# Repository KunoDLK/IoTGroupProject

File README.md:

# Project:

## Waste Management Optimization:

Problem: Static bin collection routes can leave many bins overflowing
Solution: Create a smart waste management system with fill-level so the council can optimes bin collection
Sensors: Ultrasonic distance sensors measure bin fill levels; Weight Sensor to approximate waste density; Air Monitoring for potential pollution cause by waste

## Work split:

Kuno:
- Hardware:
  - PCB
  - mounting + assembly
- Firmware:
  - Reading sensors
  - Sending data to cloud
- Creating Fake Data

Mark & Andrea:
- Cloud:
  - Server
- Application:
  - Collecting data from MQTT
  - displaying the data
  - Figure out which bin needs to be collected next

## The data:

- Current Data:
  - Temp
  - humidity
  - Fill Level
  - Weight
  - Density
- Daily Data:
  - Day high Temp
  - Day Low Temp
  - Day Fill delta
- Counters:
  - Time Since Emptied
  - Time Since Full
  - Number of fills
- Server Data
  - trends ect.

## MQTT:

URL:
c79e2ea5e65e40f6b79ba3a3aad7c19f.s1.eu.hivemq.cloud
Port:
8883
Websocket Port:
8884

User:admin
Password:Password1  

## MQTT Websocket Client
https://www.hivemq.com/demos/websocket-client/

## MQTT Data:

### Data Organisation:
{Postcode area code}/{Street Name}/{House Number}

TS16/FORMBY_WALK/01/

### Sensor Data
./Sensors/Current
{
  "fillLevel": 75,
  "weight": 15.4,
  "density": 1.2
} 

### Environment Data
./Environment/Current
{
  "temp": 22.5,
  "humidity": 60
}

./Environment/Daily
{
  "low": 5.5,
  "high" 22
}

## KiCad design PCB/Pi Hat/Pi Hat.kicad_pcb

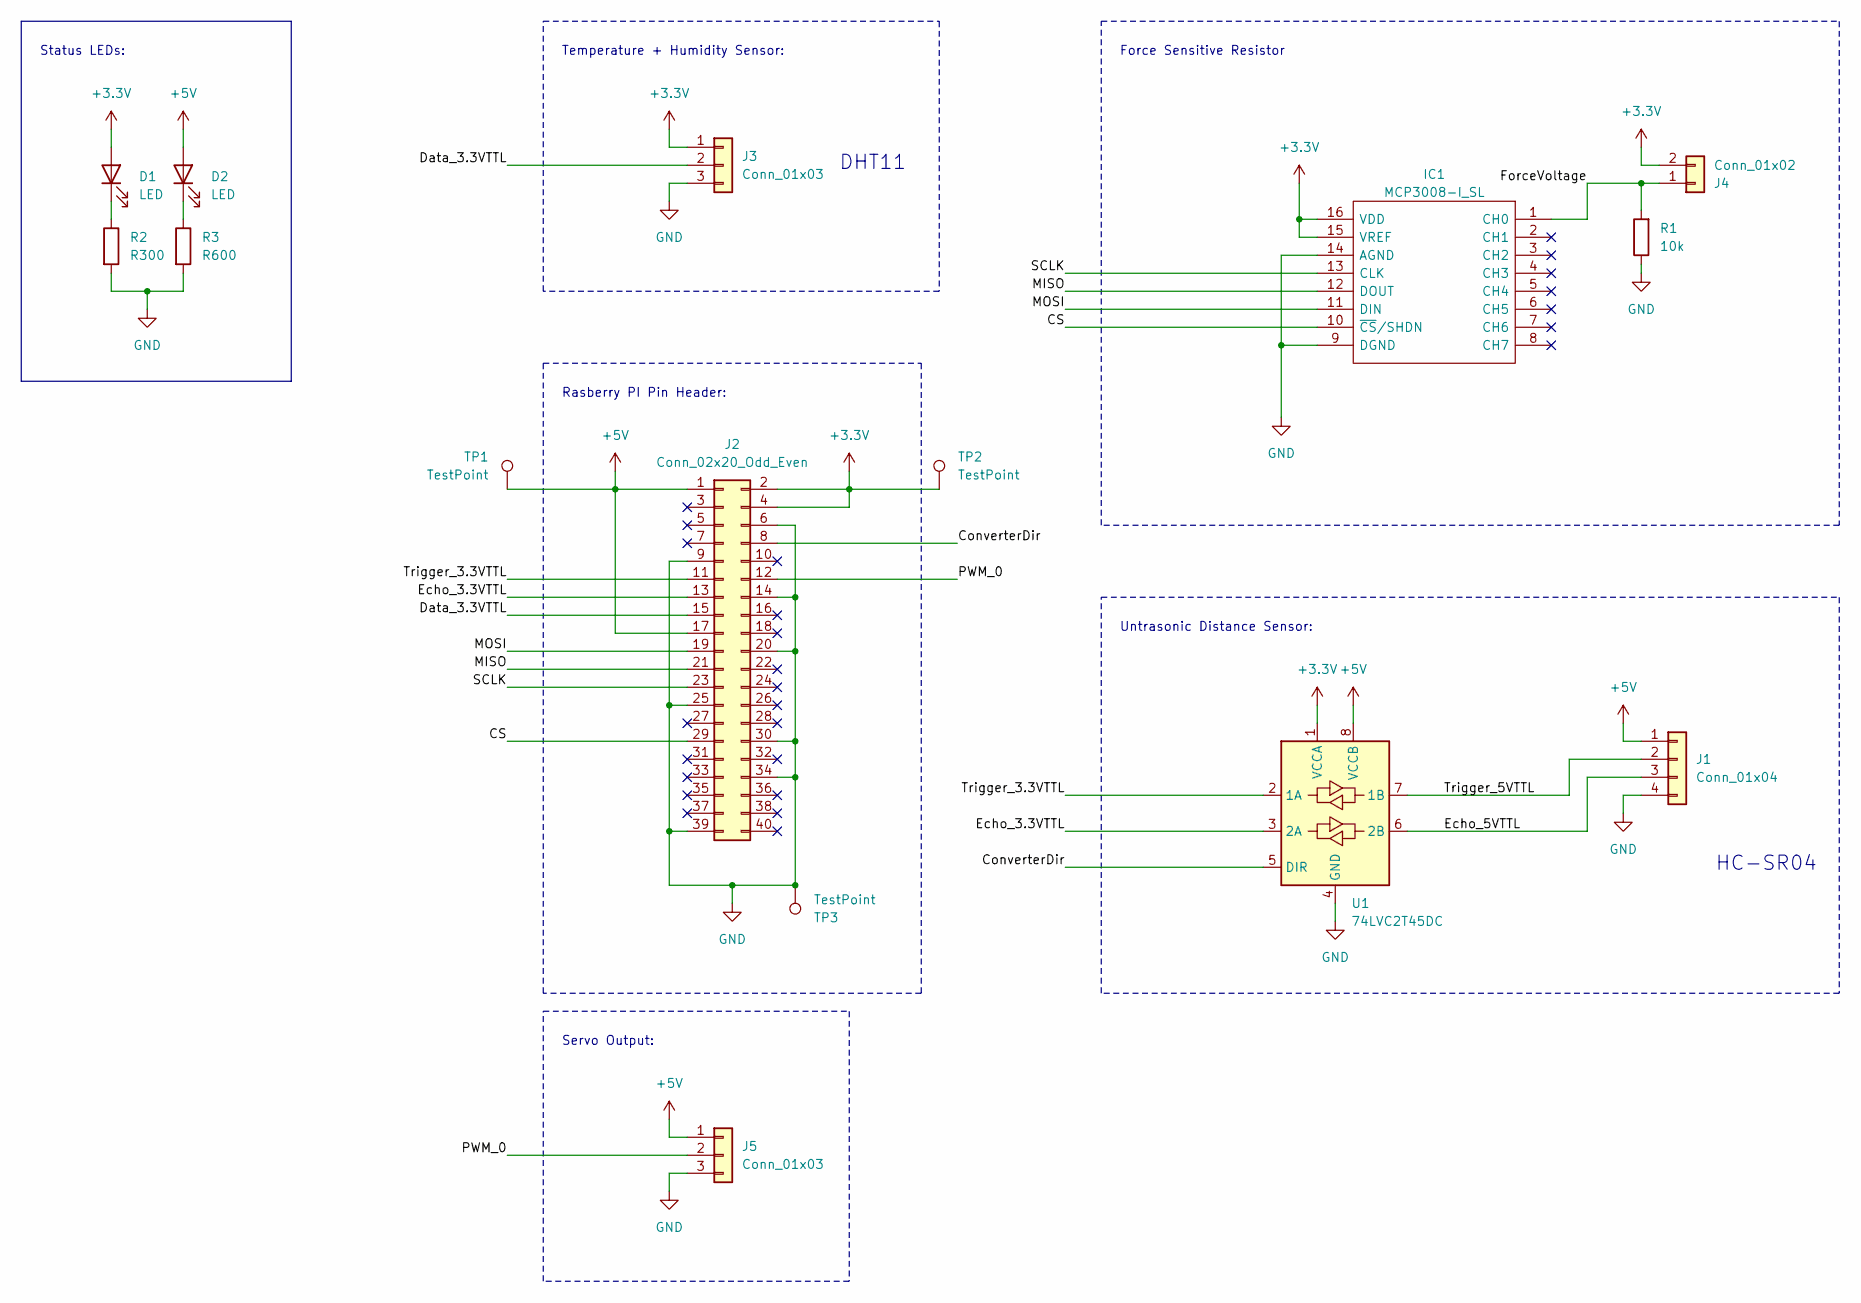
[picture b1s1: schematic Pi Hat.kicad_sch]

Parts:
D1, D2: LED; LED_0805_2012Metric
IC1: MCP3008-I_SL; DIP-16_W7.62mm_Socket; Manufacturer_Part_Number MCP3008-I/SL; Mouser Part Number 579-MCP3008-I/SL
J1: Conn_01x04; Molex_KK-254_AE-6410-04A_1x04_P2.54mm_Vertical
J2: Conn_02x20_Odd_Even; PinSocket_2x20_P2.54mm_Vertical
J3, J5: Conn_01x03; Molex_KK-254_AE-6410-03A_1x03_P2.54mm_Vertical
J4: Conn_01x02; Molex_KK-254_AE-6410-02A_1x02_P2.54mm_Vertical
R1: 10k; R_0805_2012Metric
R2: R300; R_0805_2012Metric
R3: R600; R_0805_2012Metric
TP1, TP2, TP3: TestPoint; TestPoint_Pad_D3.0mm
U1: 74LVC2T45DC; VSSOP-8_2.3x2mm_P0.5mm

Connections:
+3.3V: D1.2 (A), IC1.15 (VREF), IC1.16 (VDD), J2.2, J2.4, J3.1, J4.2, TP2.1, U1.1 (VCCA)
+5V: D2.2 (A), J1.1, J2.1, J2.17, J5.1, TP1.1, U1.8 (VCCB)
/CS: IC1.10 (~CS/SHDN), J2.29
/ConverterDir: J2.8, U1.5 (DIR)
/Data_3.3VTTL: J2.15, J3.2
/Echo_3.3VTTL: J2.13, U1.3 (2A)
/Echo_5VTTL: J1.3, U1.6 (2B)
/ForceVoltage: IC1.1 (CH0), J4.1, R1.2
/MISO: IC1.12 (DOUT), J2.21
/MOSI: IC1.11 (DIN), J2.19
/PWM_0: J2.12, J5.2
/SCLK: IC1.13 (CLK), J2.23
/Trigger_3.3VTTL: J2.11, U1.2 (1A)
/Trigger_5VTTL: J1.2, U1.7 (1B)
GND: IC1.9 (DGND), IC1.14 (AGND), J1.4, J2.6, J2.9, J2.14, J2.20, J2.25, J2.30, J2.34, J2.39, J3.3, J5.3, R1.1, R2.2, R3.2, TP3.1, U1.4 (GND)
unnamed: D1.1 (K), R2.1
unnamed: D2.1 (K), R3.1

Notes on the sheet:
Untrasonic Distance Sensor:
Servo Output:
Force Sensitive Resistor
Status LEDs:
DHT11
Temperature + Humidity Sensor:
Rasberry PI Pin Header:
HC-SR04

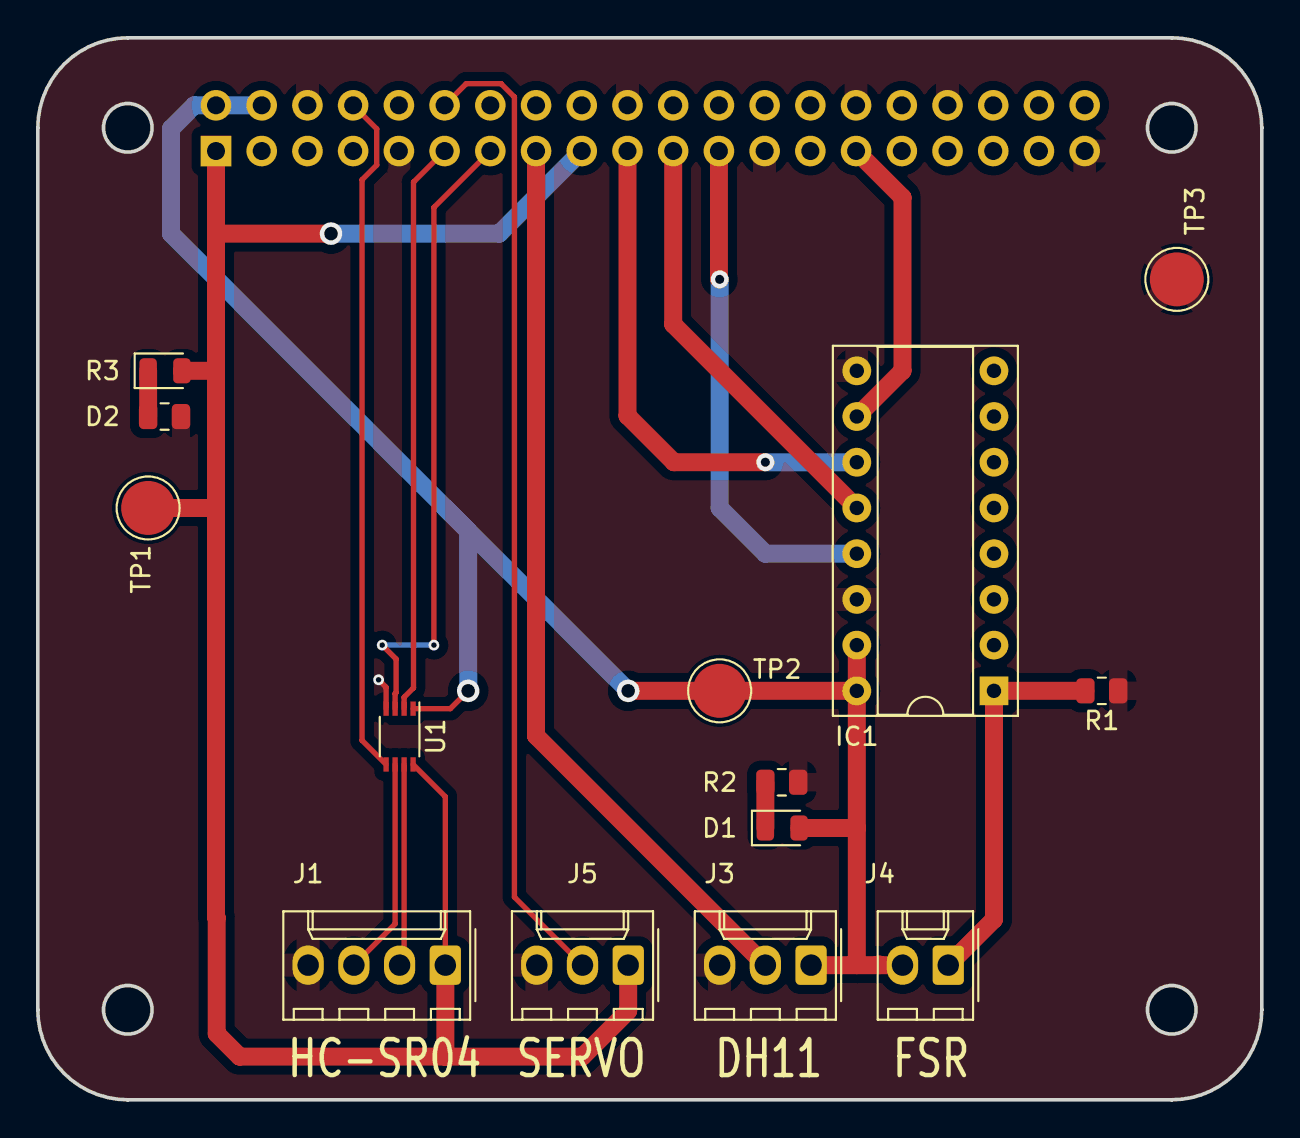
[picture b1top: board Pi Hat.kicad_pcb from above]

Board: 2 copper layers, 68.0 x 59.0 mm, 15 parts (1 on the bottom side), 17 nets.

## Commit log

2025-01-23 Added initial README
2025-01-30 Added GitIgnore
2025-01-30 Added example code for temp/humid Sensor DH11
2025-01-30 Added PI Hat PCB
2025-01-30 completed PCB
2025-01-30 Experted fabrication files
2025-01-30 updated PCB
2025-02-03 added 3d design files
2025-02-03 completed placement of ultrasonic sensor
2025-02-04 completed mounting for PI
2025-02-27 complete PCB
2025-02-27 DFM check adjustments
2025-04-03 restructured binPOC model. smaller platform with dovetail joints
2025-04-03 Updated model
2025-04-03 adjusted dovetail joints for strength
2025-04-06 made adjustments to pi holder for better sonic fitment
2025-04-06 exported binPOC stl
2025-04-06 changed file name
2025-04-06 renamed top platform
2025-04-06 created FSR base support
2025-04-06 exported STL
2025-04-07 update design parameters for fitment
2025-04-15 added straight beam
2025-04-15 completed weight platform
2025-04-16 updated dimensions
2025-04-16 updated print file
2025-04-16 Add .gitattributes and .gitignore.
2025-04-16 Add project files.
2025-04-16 Pre-spike icons added to chart
2025-04-16 Added trends and spike notifications
2025-04-16 Controller methods refactor to use services
2025-04-16 Implemented Ajax and associated partial
2025-04-16 Add map view and latitude/longitude support
    Updated DashboardController to include ApplicationDbContext and new Map action method. Added Latitude and Longitude properties to SensorReadings table and related files. Enhanced Index.cshtml with ma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
2025-04-16 exported platform
2025-04-16 Introduced dummy data, some glitches
2025-04-16 Add XML docs and update comments in various files
    Added XML documentation comments to multiple classes and methods
    to enhance code readability and maintainability. Updated the
    comment in Program.cs to generalize background service
    registration. Removed commented-out code in _TrendChart.cshtml
    and updated the welcome message in Index.cshtml to display
    "Bindicator" and list prototype features.
2025-04-16 Comments updates
2025-04-17 ML script to predict bin collection
    ML script to predict bin collection
2025-04-17 Added in dummy data seeder
2025-04-17 Commit to main
2025-04-17 Seeder update
2025-04-17 full bin prediction started
2025-04-17 added rim around weight platform base
2025-04-17 added script
2025-04-21 Updated gitignore
2025-04-21 added spec
2025-04-22 completed support beams
2025-04-23 updated MQTT script
2025-04-23 added mock implemetations for sensors
2025-04-23 change voltage scaler
2025-04-23 added ADC reading to MQTT loop
2025-04-24 cleaned up enviroment
2025-04-24 updated scrip to send temp data
2025-04-24 updated support beams
2025-04-24 Add IoT Report - Missing parts to be filled
2025-04-26 completed firmware. all sensors working + mqtt intergration
2025-04-27 updated 3d print file
2025-04-27 changed sleep time between sending sensor data
2025-04-27 added location data
2025-05-01 removed bindicator
2025-05-01 added bindicator
2025-05-01 new regression script
2025-05-01 Add json example
2025-05-01 update git ignore
2025-05-01 updated link to web app
2025-05-01 updated link to Bindicator
2025-05-01 updated report with my parts
2025-05-01 updated Bindicator
2025-05-01 added group report
